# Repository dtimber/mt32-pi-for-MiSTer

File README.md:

# mt32-pi-for-MiSTer
mt32-pi design for MiSTer FPGA based on RPi Zero 2 W

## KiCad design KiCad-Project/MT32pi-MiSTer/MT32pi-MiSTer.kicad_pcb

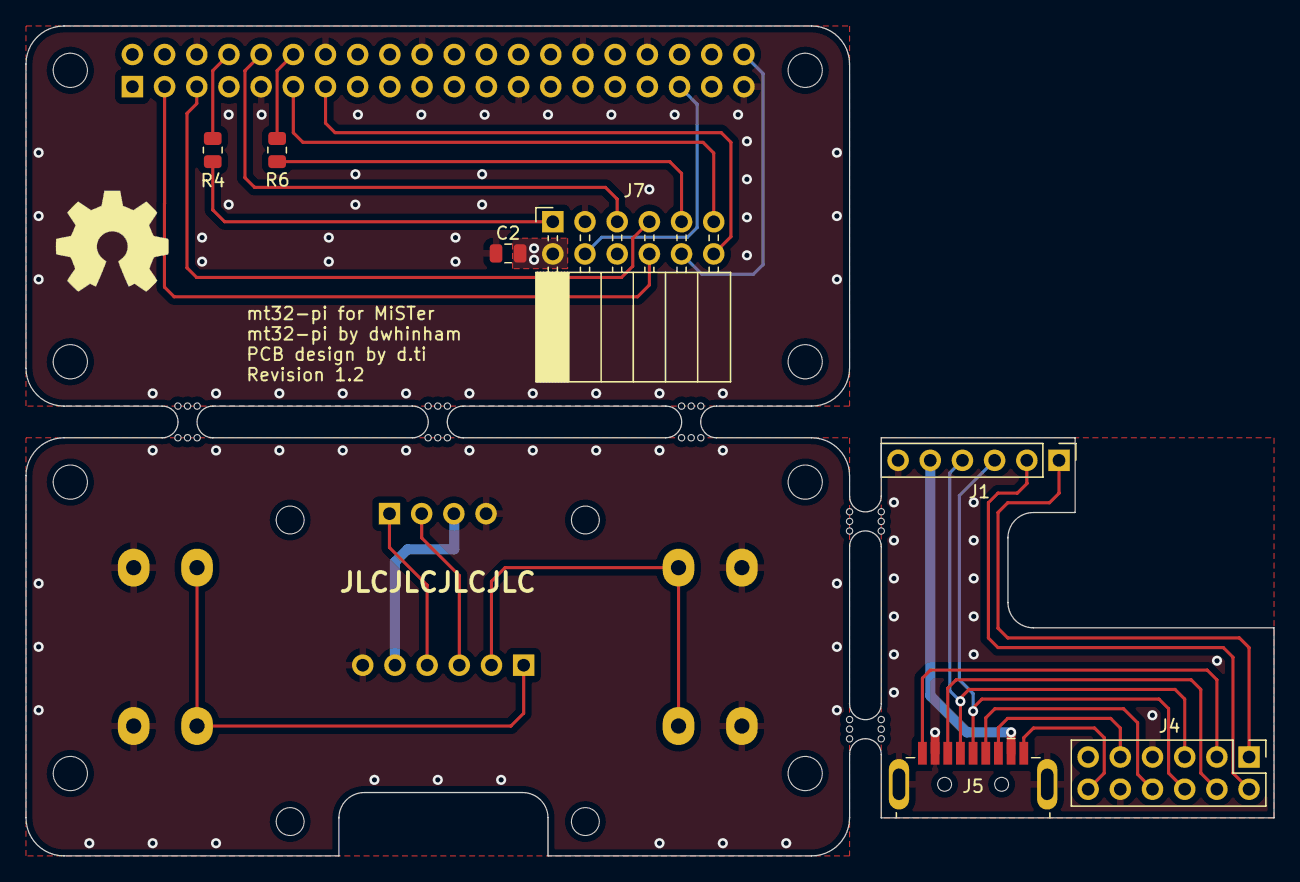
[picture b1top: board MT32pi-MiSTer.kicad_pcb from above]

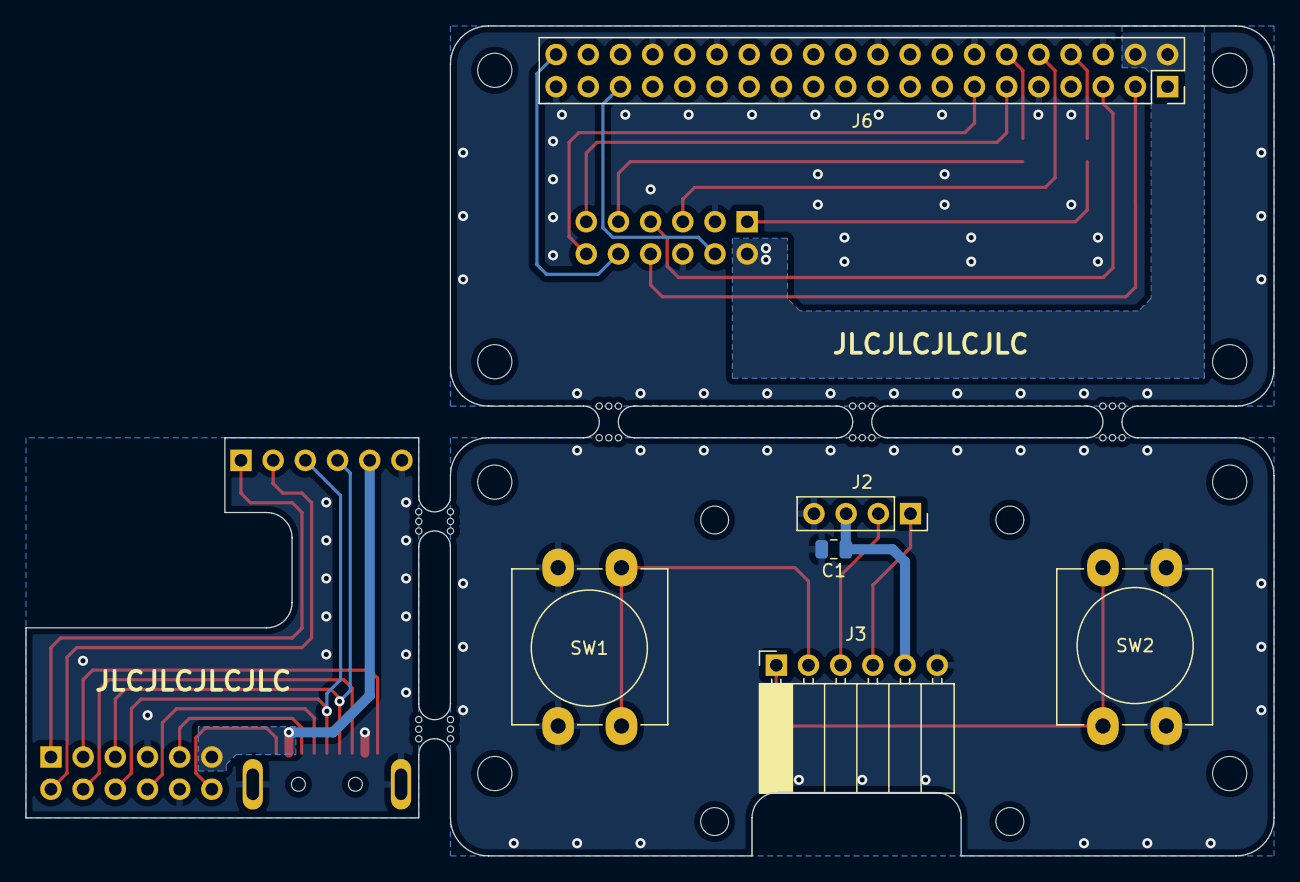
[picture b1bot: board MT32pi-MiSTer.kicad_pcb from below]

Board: 2 copper layers, 98.5 x 65.5 mm, 25 parts (6 on the bottom side), 30 nets.

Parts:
C1, C2: 10uF; C_0805_2012Metric
H1, H2, H3, H4, H5, H6, H7, H8: M2.5; MountingHole_2.7mm_M2.5
H9, H10, H11, H12: M2; MountingHole_2.2mm_M2
J1: Interconnector Front; PinHeader_1x06_P2.54mm_Vertical
J2: OLED; PinSocket_1x04_P2.54mm_Vertical
J3: Frontpanel Connector; PinSocket_1x06_P2.54mm_Horizontal
J4: Interconnector Back; PinHeader_2x06_P2.54mm_Vertical
J5: USB3_A; USB3_A_Plug_Wuerth_692112030100_Horizontal
J6: RPI; PinSocket_2x20_P2.54mm_Vertical
J7: Backpanel Connector; PinSocket_2x06_P2.54mm_Horizontal
R4: NP; R_0805_2012Metric
R6: 100R; R_0805_2012Metric
SW1, SW2: 430476085716; SW_PUSH-12mm_Wuerth-430476085716

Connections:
/BP_5V: C2.1, J6.2, J6.4, J7.2
/BP_BTN1: J6.11, J7.11
/BP_BTN2: J6.13, J7.12
/BP_GND: C2.2, J6.6, J6.9, J6.14, J6.20, J6.25, J6.30, J6.34, J6.39, J7.3, J7.6
/BP_PCM_CLK: J7.9, R6.2
/BP_PCM_DOUT: J6.40, J7.10
/BP_PCM_FS: J6.35, J7.4
/BP_RXD: J6.10, J7.5
/BP_SCL: J6.5, J7.7
/BP_SDA: J6.3, J7.8
/BP_TXD: J7.1, R4.2
/BTN1: J1.2, J4.2
/BTN2: J1.1, J4.1
/FP_5V: C1.1, J2.3, J3.5
/FP_BTN1: J3.2, SW1.1
/FP_BTN2: J3.1, SW2.1
/FP_GND: C1.2, J2.4, J3.6, SW1.2, SW2.2
/FP_SCL: J2.2, J3.3
/FP_SDA: J2.1, J3.4
/PCM_CLK: J4.4, J5.6 (SSRX+)
/PCM_DOUT: J4.3, J5.5 (SSRX-)
/PCM_FS: J4.9, J5.8 (SSTX-)
/RXD: J4.8, J5.2 (D-)
/SCL: J1.3, J4.6, J5.7 (DRAIN)
/SDA: J1.4, J4.5, J5.3 (D+)
/TXD: J4.12, J5.9 (SSTX+)
GND: J1.6, J4.7, J4.10, J5.4 (GND), J5.10 (SHIELD)
unnamed: J6.8, R4.1
unnamed: J6.12, R6.1
VBUS: J1.5, J4.11, J5.1 (VBUS)
